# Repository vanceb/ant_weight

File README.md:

# ant_weight
Ant Weight robot design

My first attempt at building an ant-weight fighting robot.  Initial version is really a prototype and is unlikely to be entered in to competition, it is mainly to test out some of the control and design ideas.

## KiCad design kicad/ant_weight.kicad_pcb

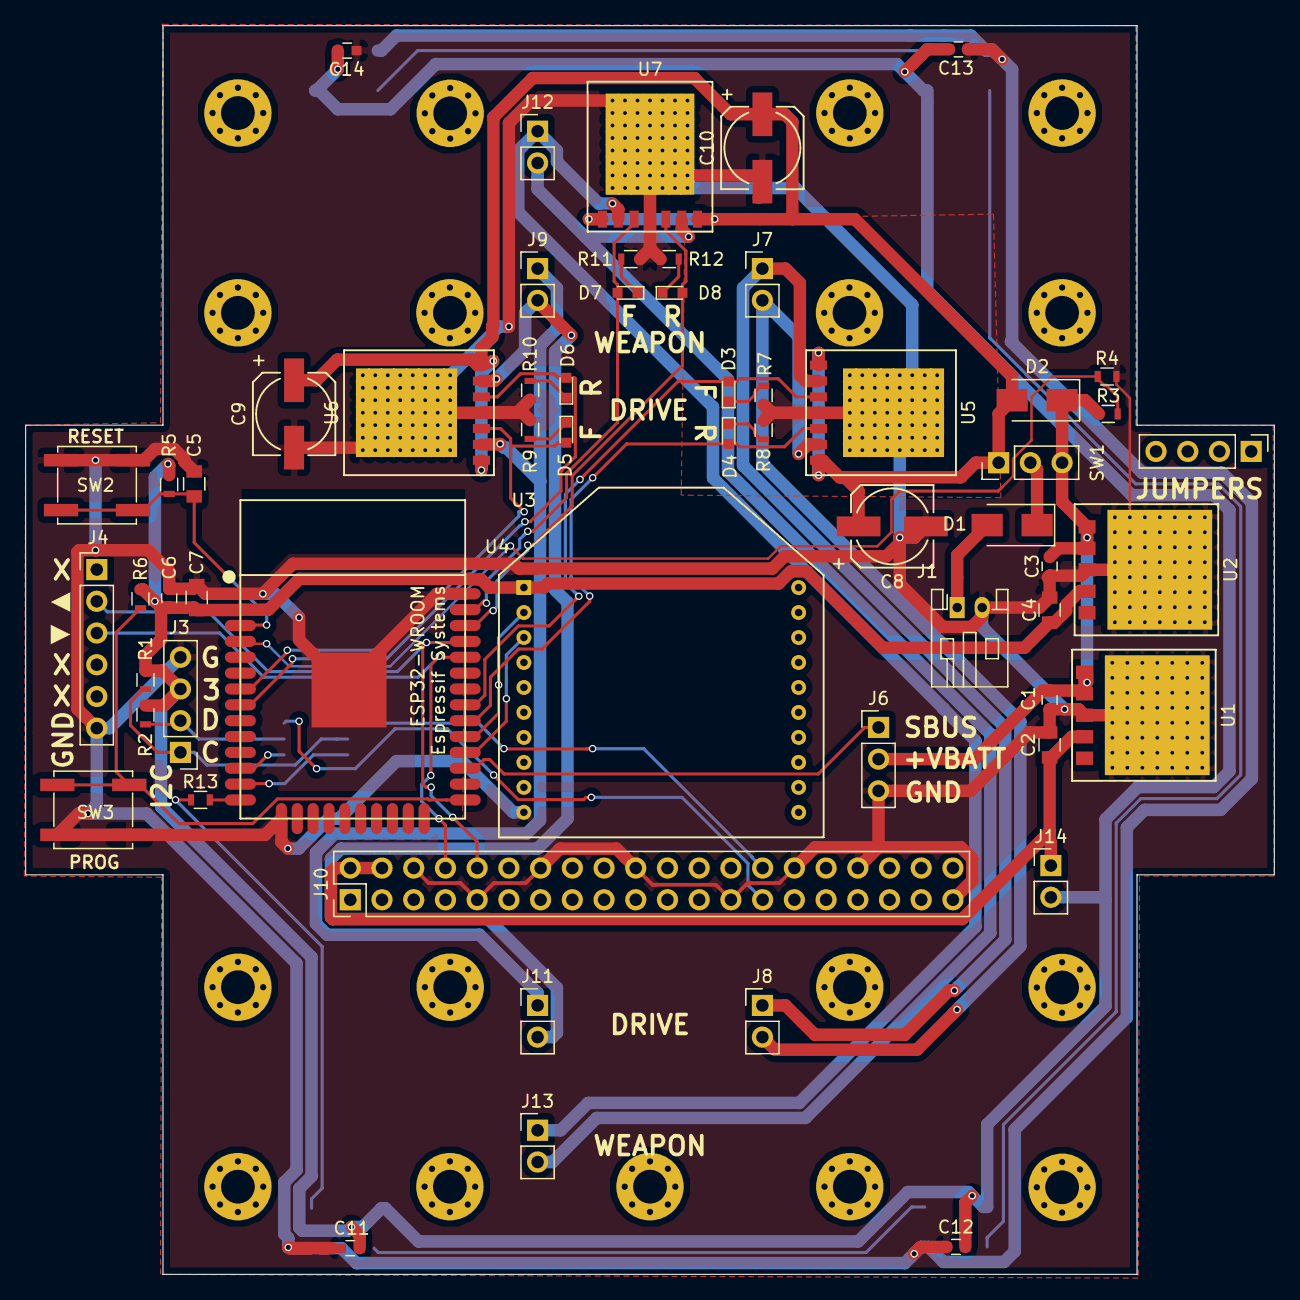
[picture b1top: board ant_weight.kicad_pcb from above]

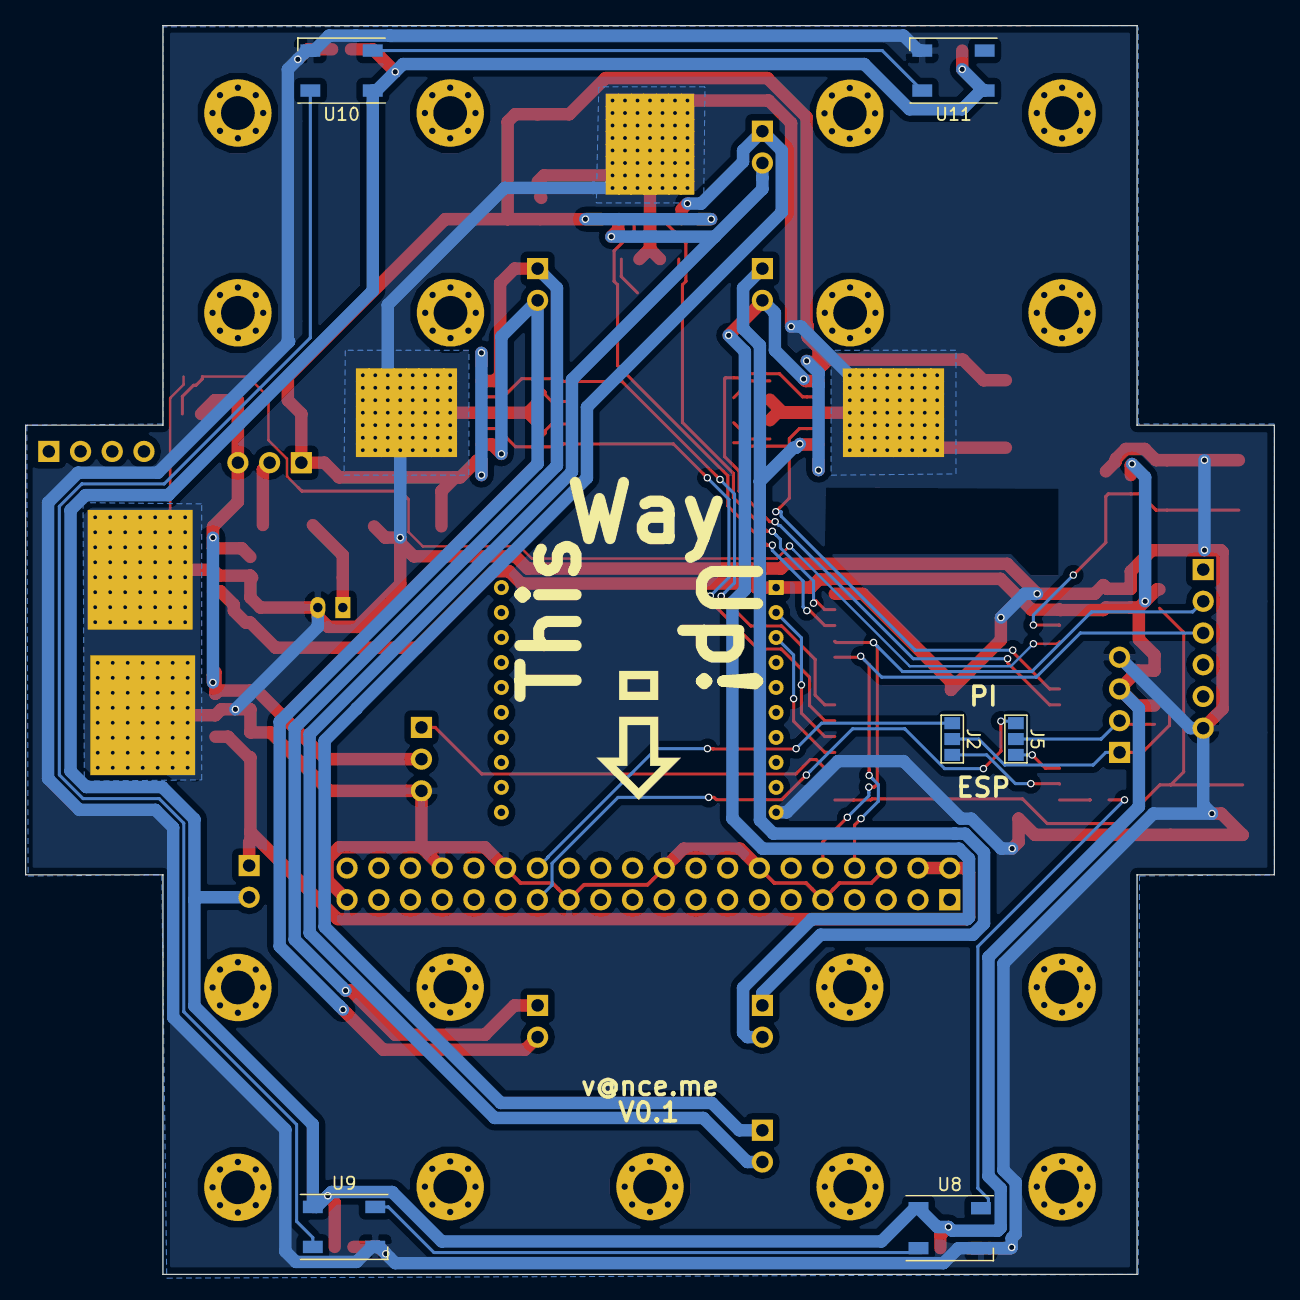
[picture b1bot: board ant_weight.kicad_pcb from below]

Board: 2 copper layers, 100.0 x 100.0 mm, 63 parts (6 on the bottom side), 44 nets.

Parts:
C1, C3, C6, C11, C12, C13, C14: 0.1uF; C_0603
C2, C4, C7: 10uF; C_0805
C5: 1uF; C_0805
C8, C9, C10: 10uF; c_elec_6.3x7.7
D1, D2: D_Schottky; D_SMA
D3, D4, D5, D6, D7, D8: LED; LED_0603
J1: BATT_JST; JST_PH_S2B-PH-K_02x2.00mm_Angled
J2, J5: GS3
J3: I2C; Pin_Header_Straight_1x04_Pitch2.54mm
J4: FTDI; Pin_Header_Straight_1x06_Pitch2.54mm
J6: SBus Rx; Pin_Header_Straight_1x03_Pitch2.54mm
J7: RL; Pin_Header_Straight_1x02_Pitch2.54mm
J8: FL; Pin_Header_Straight_1x02_Pitch2.54mm
J9: RR; Pin_Header_Straight_1x02_Pitch2.54mm
J10: Pi Header; Pin_Header_Straight_2x20_Pitch2.54mm
J11: FR; Pin_Header_Straight_1x02_Pitch2.54mm
J12: RW; Pin_Header_Straight_1x02_Pitch2.54mm
J13: FW; Pin_Header_Straight_1x02_Pitch2.54mm
J14: 3V3 Only; Pin_Header_Straight_1x02_Pitch2.54mm
R1, R2: 4k7; R_0603
R3: 47k; R_0603
R4: 22k; R_0603
R5, R6: 10k; R_0603
R7, R8, R9, R10, R11, R12: 330; R_0603
R13: 100; R_0603
SW1: POWER; Pin_Header_Straight_1x03_Pitch2.54mm
SW2: RESET; SW_SPST_EVPBF
SW3: PROGRAM; SW_SPST_EVPBF
U1: BA50DD0WHFP; HRP5
U2: BA33DD0WHFP; HRP5
U3: XBee; XBEE
U4: ESP32-WROOM
U5, U6, U7: BD622xxx; HRP7
U8, U9, U10, U11: WS2812B; LED_WS2812B-PLCC4

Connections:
+3V3: C4.1, C6.1, C7.1, C11.1, C12.1, C13.1, C14.1, J3.3, J14.2, R1.1, R2.1, R5.1, R6.1, U2.4, U3.1, U4.2, U8.1, U9.1, U10.1, U11.1
+5V: C2.1, J10.2, J10.4, J14.1, U1.4
+BATT: D1.1, SW1.2
BATT_SENSE: R3.2, R4.1, U4.4
E_SCL: J2.1, U4.13
E_SDA: J5.1, U4.12
GND: C1.2, C2.2, C3.2, C4.2, C5.2, C6.2, C7.2, C8.2, C9.2, C10.2, C11.2, C12.2, C13.2, C14.2, J1.2, J3.4, J4.6, J6.3, J10.6, J10.9, J10.14, J10.20, J10.25, J10.30, J10.34, J10.39, R4.2, R7.2, R8.2, R9.2, R10.2, R11.2, R12.2, SW2.1, SW3.2, U1.3, U2.3, U3.10, U4.1, U4.15, U4.38, U4.39, U5.4, U5.FIN, U6.4, U6.FIN, U7.4, U7.FIN, U8.3, U9.3, U10.3, U11.3
LED: R13.2, U4.14
L_FWD: D3.2, U4.31, U5.3
L_REV: D4.2, U4.30, U5.5
unnamed: C5.1, R5.2, SW2.2, U4.3
unnamed: D1.2, J1.1
unnamed: D3.1, R7.1
unnamed: D4.1, R8.1
unnamed: D5.1, R9.1
unnamed: D6.1, R10.1
unnamed: D7.1, R11.1
unnamed: D8.1, R12.1
unnamed: J7.1, J8.1, U5.2
unnamed: J7.2, J8.2, U5.6
unnamed: J9.1, J11.1, U6.2
unnamed: J9.2, J11.2, U6.6
unnamed: J12.1, J13.1, U7.2
unnamed: J12.2, J13.2, U7.6
unnamed: R6.2, SW3.1, U4.25
unnamed: R13.1, U8.4
unnamed: U8.2, U9.4
unnamed: U10.2, U11.4
unnamed: U9.2, U10.4
P_SCL: J2.3, J10.28
P_SDA: J5.3, J10.27
RXD0: J4.3, J10.8, U4.34
R_FWD: D5.2, U4.7, U6.3
R_REV: D6.2, U4.8, U6.5
SBUS: J6.1, U4.27
SCL: J2.2, J3.1, R1.2
SDA: J3.2, J5.2, R2.2
TXD0: J4.2, J10.10, U4.35
V_ELEC: C1.1, C3.1, D2.1, J6.2, R3.1, SW1.3, U1.1, U1.2, U2.1, U2.2
V_MOTOR: C8.1, C9.1, C10.1, D2.2, SW1.1, U5.1, U5.7, U6.1, U6.7, U7.1, U7.7
W_FWD: D7.2, U4.37, U7.3
W_REV: D8.2, U4.36, U7.5
XBRX: U3.2, U4.29
XBTX: U3.3, U4.28

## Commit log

2018-07-19 Version 0.1 board design submitted for manufacture
2018-07-31 Solder mask and BOM for v0.1
2018-07-31 Initial code
2018-07-31 Moved R_FWD from IO35 to IO33, because IO35 is input only
2018-08-13 Remote control working
2018-08-19 Added sensitivity to the controls for speed and turn
2018-08-19 Upgraded to kicad v5
2018-08-19 Tidies and commented, added switch processing and allowed for inversion of steering based on switch position
2018-08-22 Refactored to take the display code out of the main program
2018-08-26 Updated weapon control to be modified by switch position
2018-08-29 Added new light displays controlled by the switches
2018-08-29 Added .gitignore to the code directory
2018-08-29 Corrected copy and paste error on steering code and tidied light modes
2018-08-29 Updated display framerate
2018-09-09 Minot changes to lights display
2018-09-19 Updated esp-idf to latest version
2018-09-19 Increased stack for lights task, and braked weapon motor rather than left it undriven
